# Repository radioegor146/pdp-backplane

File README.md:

# pdp-backplane

Custom PDP-11 Q22/Q22 backplane

All schematic is in KiCad

~~For now, not tested, so use on your own risk!~~

Tested, working!

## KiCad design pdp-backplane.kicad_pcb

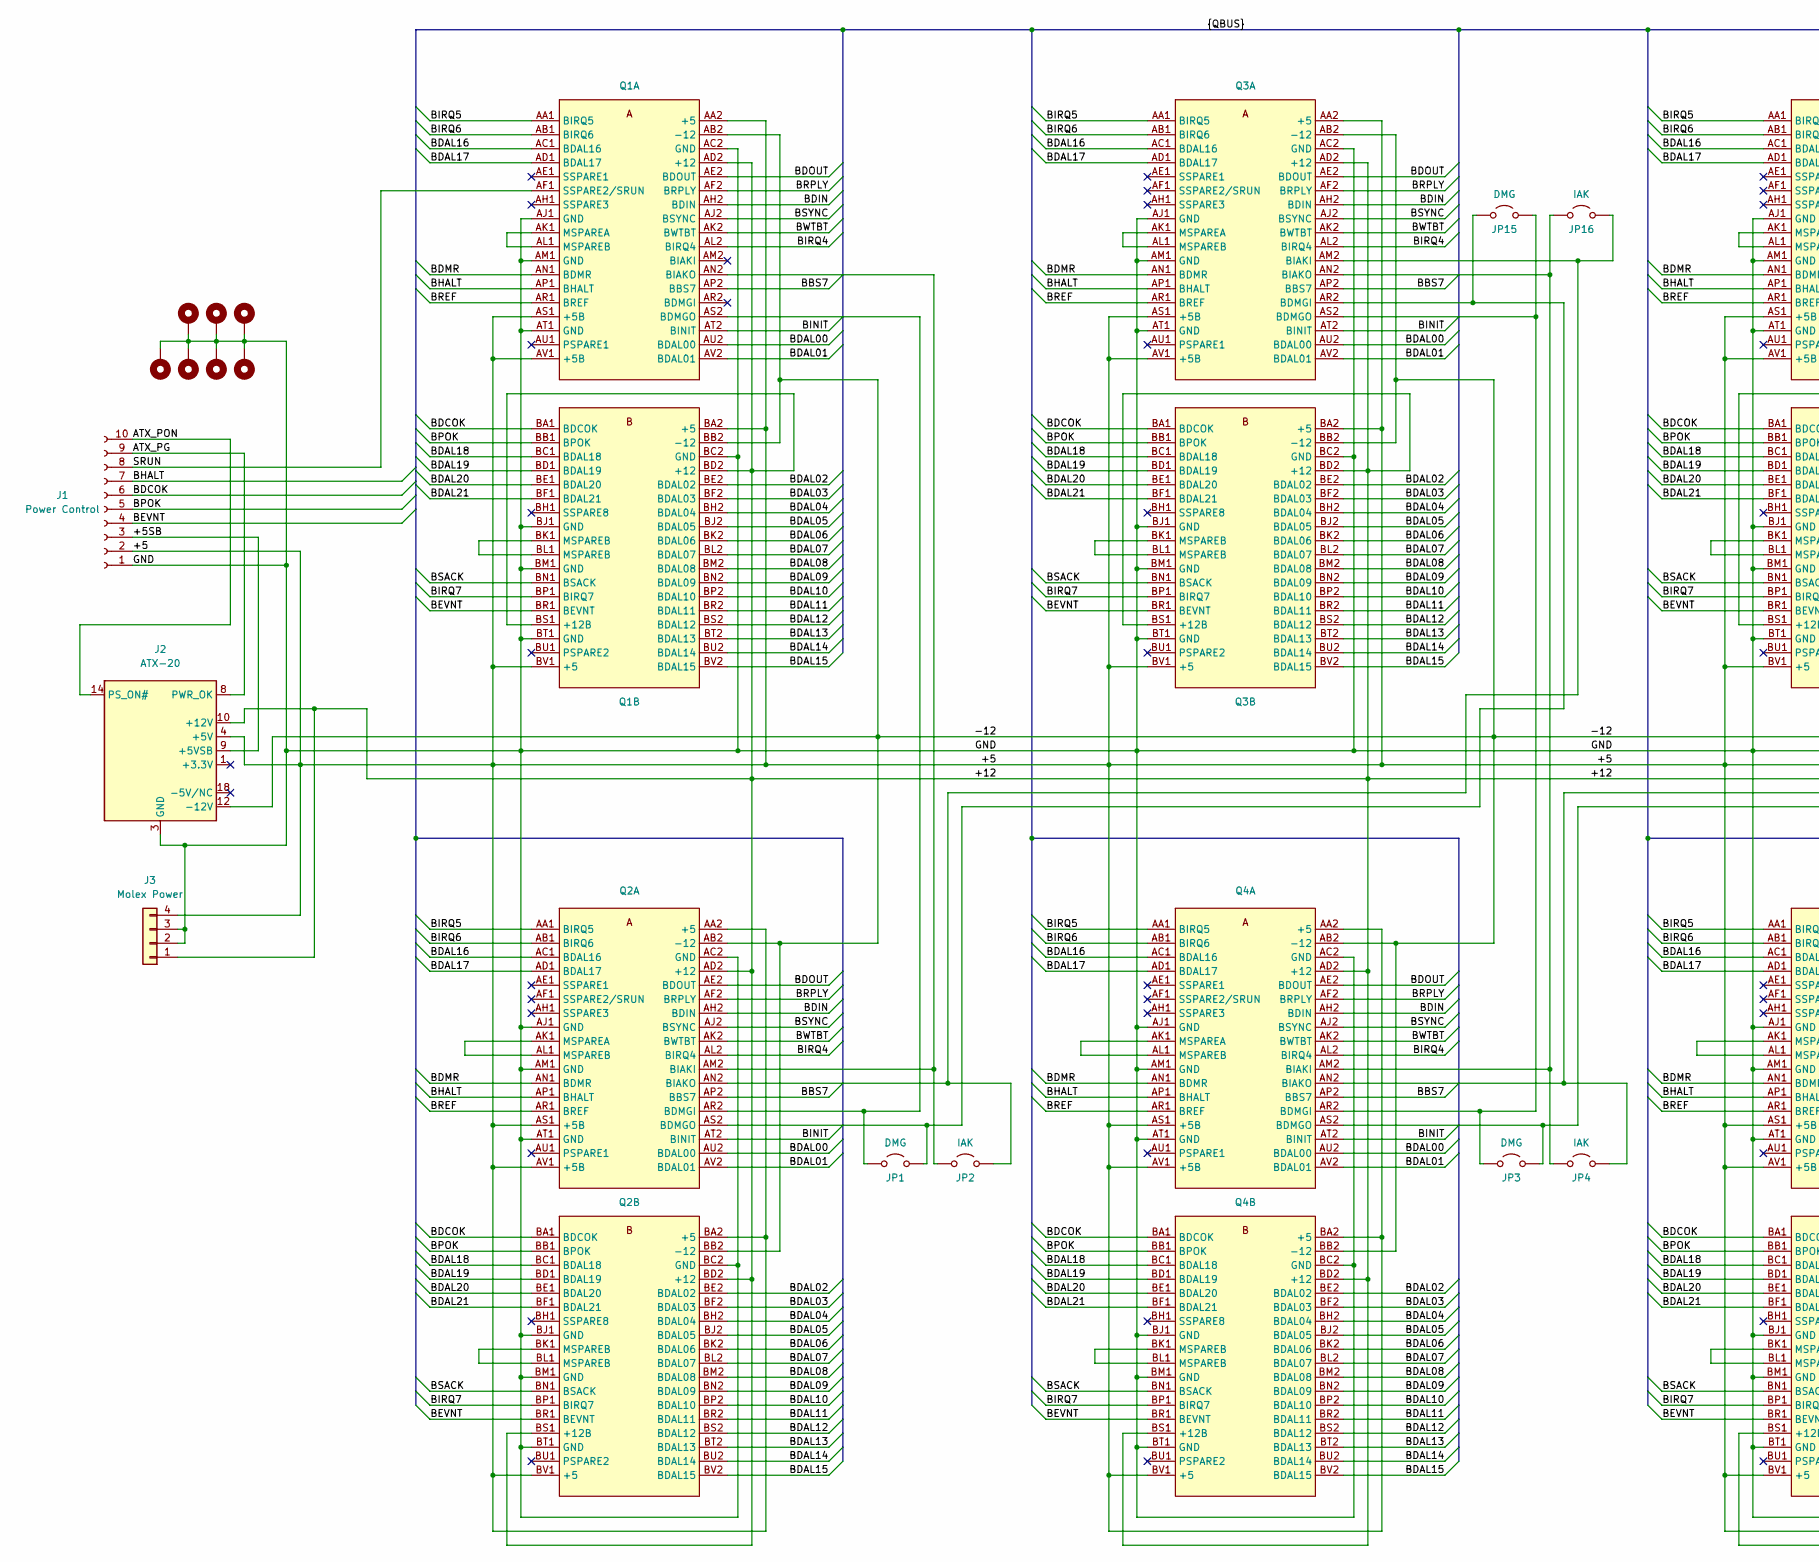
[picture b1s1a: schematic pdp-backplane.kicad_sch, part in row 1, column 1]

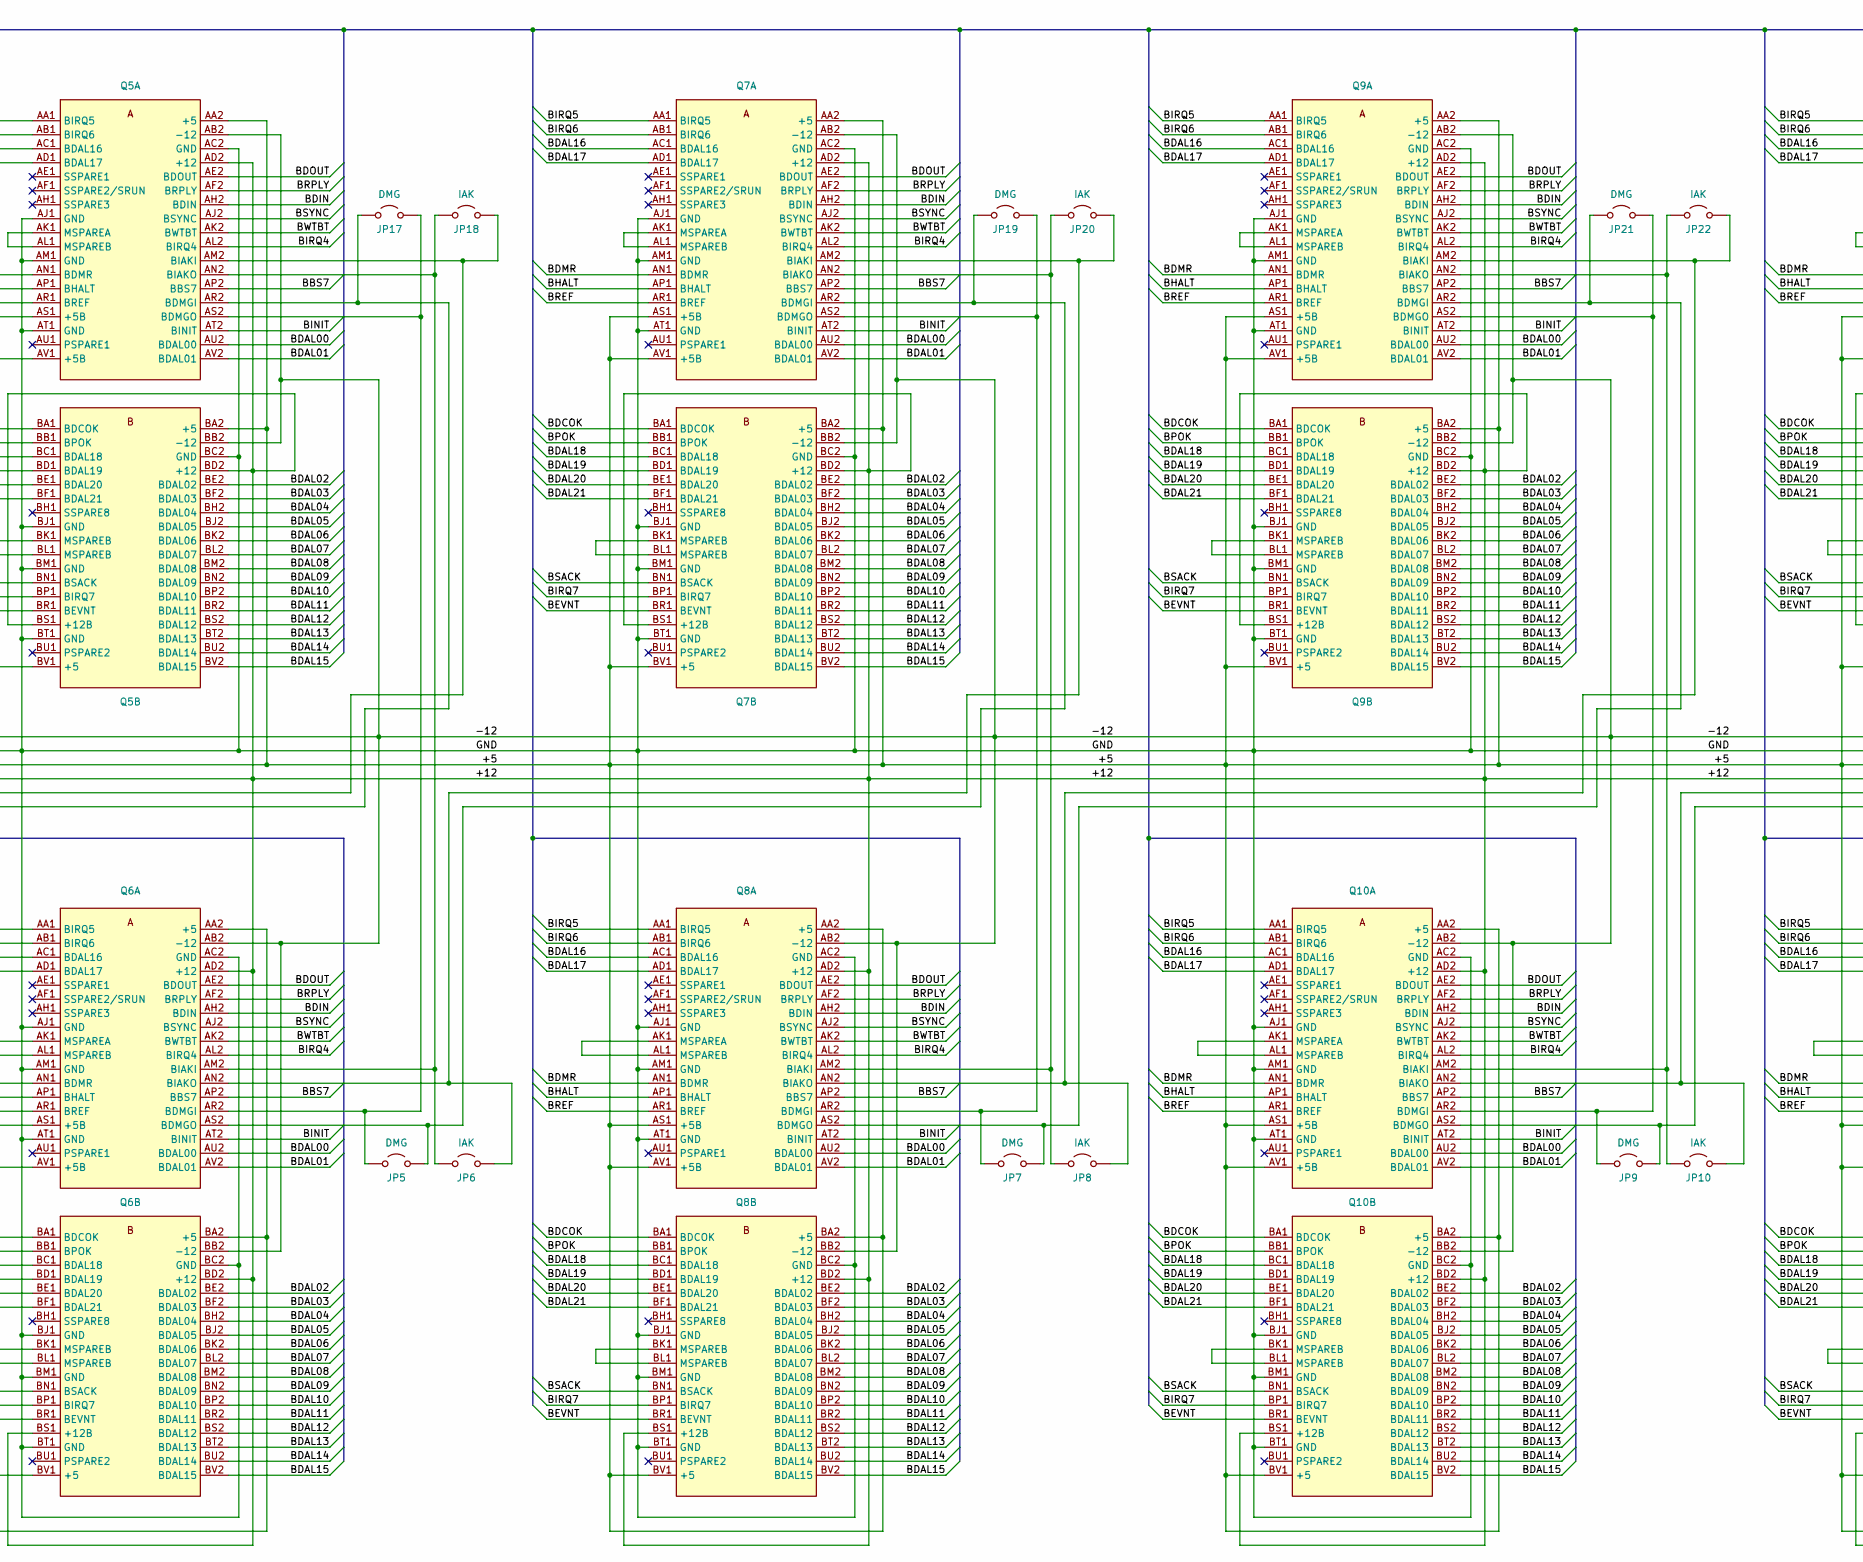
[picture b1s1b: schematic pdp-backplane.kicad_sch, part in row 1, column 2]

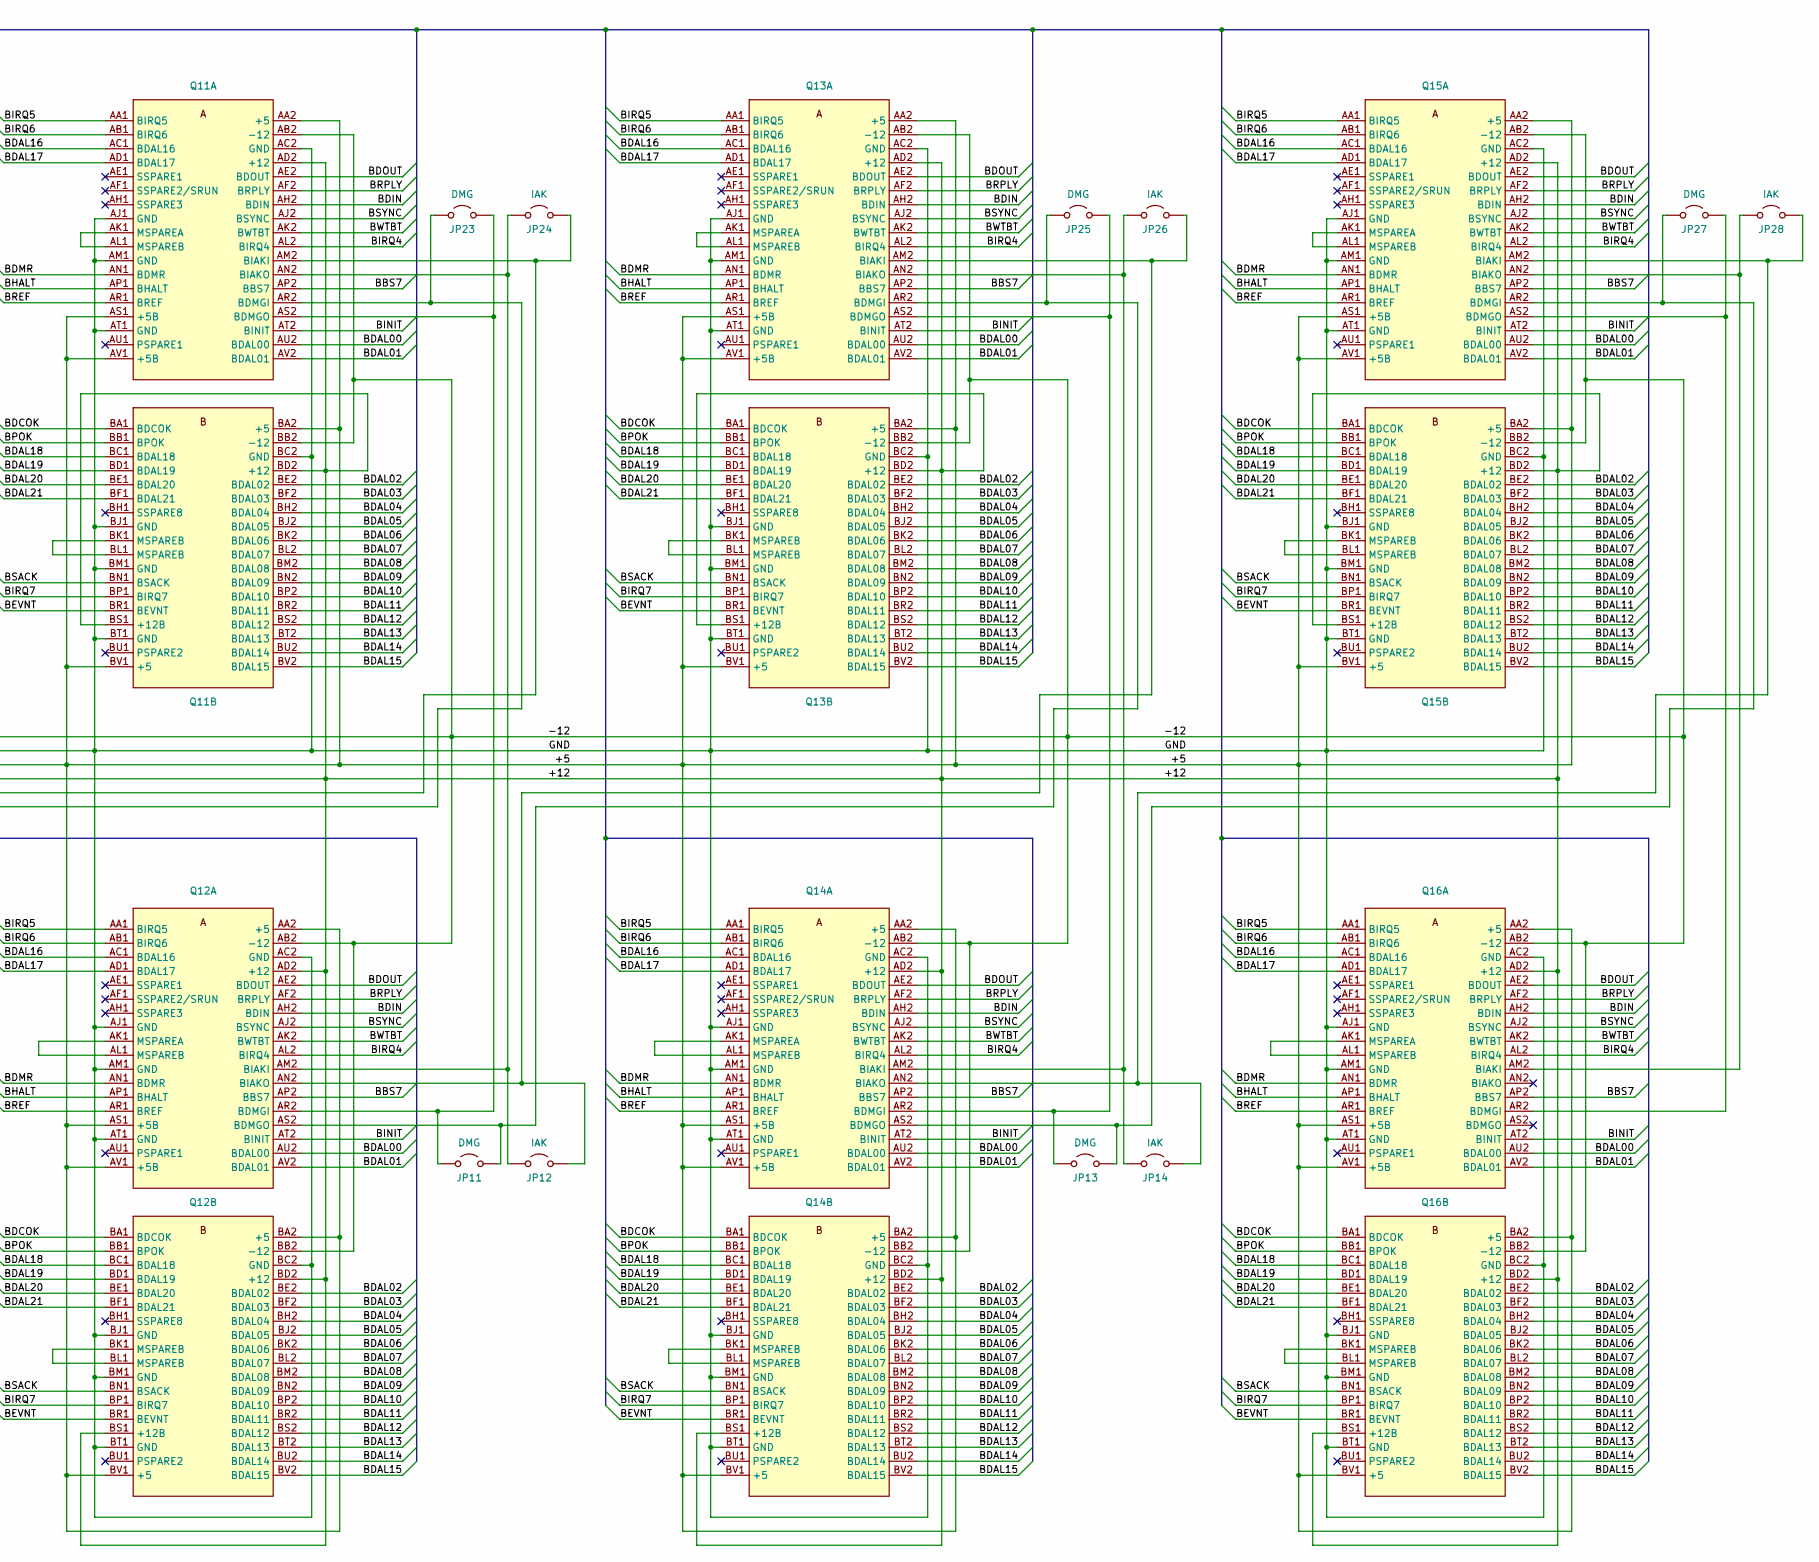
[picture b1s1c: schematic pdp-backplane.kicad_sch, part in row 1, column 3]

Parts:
H2, H3, H4, H5, H6, H7, H8: MountingHole_Pad; MountingHole_4.3mm_M4_Pad_TopBottom
J1: Power Control; JST_XH_B10B-XH-A_1x10_P2.50mm_Vertical
J2: ATX-20; Molex_Mini-Fit_Jr_5566-20A_2x10_P4.20mm_Vertical
J3: Molex Power; TE_MATE-N-LOK_350211-1_1x04_P5.08mm_Vertical
JP1, JP3, JP5, JP7, JP9, JP11, JP13, JP15, JP17, JP19, JP21, JP23, JP25, JP27: DMG; PinHeader_1x02_P2.54mm_Vertical
JP2, JP4, JP6, JP8, JP10, JP12, JP14, JP16, JP18, JP20, JP22, JP24, JP26, JP28: IAK; PinHeader_1x02_P2.54mm_Vertical
Q1, Q2, Q3, Q4, Q5, Q6, Q7, Q8, Q9, Q10, Q11, Q12, Q13, Q14, Q15, Q16: Bus_QBUS; QBus

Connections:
/+5: J1.2, J2.4 (+5V), J2.6 (+5V), J2.19 (+5V), J2.20 (+5V), J3.4, Q1.AA2 (+5), Q1.AS1 (+5B), Q1.AV1 (+5B), Q1.BA2 (+5), Q1.BV1 (+5), Q2.AA2 (+5), Q2.AS1 (+5B), Q2.AV1 (+5B), Q2.BA2 (+5), Q2.BV1 (+5), Q3.AA2 (+5), Q3.AS1 (+5B), Q3.AV1 (+5B), Q3.BA2 (+5), Q3.BV1 (+5), Q4.AA2 (+5), Q4.AS1 (+5B), Q4.AV1 (+5B), Q4.BA2 (+5), Q4.BV1 (+5), Q5.AA2 (+5), Q5.AS1 (+5B), Q5.AV1 (+5B), Q5.BA2 (+5), Q5.BV1 (+5), Q6.AA2 (+5), Q6.AS1 (+5B), Q6.AV1 (+5B), Q6.BA2 (+5), Q6.BV1 (+5), Q7.AA2 (+5), Q7.AS1 (+5B), Q7.AV1 (+5B), Q7.BA2 (+5), Q7.BV1 (+5), Q8.AA2 (+5), Q8.AS1 (+5B), Q8.AV1 (+5B), Q8.BA2 (+5), Q8.BV1 (+5), Q9.AA2 (+5), Q9.AS1 (+5B), Q9.AV1 (+5B), Q9.BA2 (+5), Q9.BV1 (+5), Q10.AA2 (+5), Q10.AS1 (+5B), Q10.AV1 (+5B), Q10.BA2 (+5), Q10.BV1 (+5), Q11.AA2 (+5), Q11.AS1 (+5B), Q11.AV1 (+5B), Q11.BA2 (+5), Q11.BV1 (+5), Q12.AA2 (+5), Q12.AS1 (+5B), Q12.AV1 (+5B), Q12.BA2 (+5), Q12.BV1 (+5), Q13.AA2 (+5), Q13.AS1 (+5B), Q13.AV1 (+5B), Q13.BA2 (+5), Q13.BV1 (+5), Q14.AA2 (+5), Q14.AS1 (+5B), Q14.AV1 (+5B), Q14.BA2 (+5), Q14.BV1 (+5), Q15.AA2 (+5), Q15.AS1 (+5B), Q15.AV1 (+5B), Q15.BA2 (+5), Q15.BV1 (+5), Q16.AA2 (+5), Q16.AS1 (+5B), Q16.AV1 (+5B), Q16.BA2 (+5), Q16.BV1 (+5)
/+5SB: J1.3, J2.9 (+5VSB)
/+12: J2.10 (+12V), J3.1, Q1.AD2 (+12), Q1.BD2 (+12), Q1.BS1 (+12B), Q2.AD2 (+12), Q2.BD2 (+12), Q2.BS1 (+12B), Q3.AD2 (+12), Q3.BD2 (+12), Q3.BS1 (+12B), Q4.AD2 (+12), Q4.BD2 (+12), Q4.BS1 (+12B), Q5.AD2 (+12), Q5.BD2 (+12), Q5.BS1 (+12B), Q6.AD2 (+12), Q6.BD2 (+12), Q6.BS1 (+12B), Q7.AD2 (+12), Q7.BD2 (+12), Q7.BS1 (+12B), Q8.AD2 (+12), Q8.BD2 (+12), Q8.BS1 (+12B), Q9.AD2 (+12), Q9.BD2 (+12), Q9.BS1 (+12B), Q10.AD2 (+12), Q10.BD2 (+12), Q10.BS1 (+12B), Q11.AD2 (+12), Q11.BD2 (+12), Q11.BS1 (+12B), Q12.AD2 (+12), Q12.BD2 (+12), Q12.BS1 (+12B), Q13.AD2 (+12), Q13.BD2 (+12), Q13.BS1 (+12B), Q14.AD2 (+12), Q14.BD2 (+12), Q14.BS1 (+12B), Q15.AD2 (+12), Q15.BD2 (+12), Q15.BS1 (+12B), Q16.AD2 (+12), Q16.BD2 (+12), Q16.BS1 (+12B)
/-12: J2.12 (-12V), Q1.AB2 (-12), Q1.BB2 (-12), Q2.AB2 (-12), Q2.BB2 (-12), Q3.AB2 (-12), Q3.BB2 (-12), Q4.AB2 (-12), Q4.BB2 (-12), Q5.AB2 (-12), Q5.BB2 (-12), Q6.AB2 (-12), Q6.BB2 (-12), Q7.AB2 (-12), Q7.BB2 (-12), Q8.AB2 (-12), Q8.BB2 (-12), Q9.AB2 (-12), Q9.BB2 (-12), Q10.AB2 (-12), Q10.BB2 (-12), Q11.AB2 (-12), Q11.BB2 (-12), Q12.AB2 (-12), Q12.BB2 (-12), Q13.AB2 (-12), Q13.BB2 (-12), Q14.AB2 (-12), Q14.BB2 (-12), Q15.AB2 (-12), Q15.BB2 (-12), Q16.AB2 (-12), Q16.BB2 (-12)
/ATX_PG: J1.9, J2.8 (PWR_OK)
/ATX_PON: J1.10, J2.14 (PS_ON#)
/BBS7: Q1.AP2 (BBS7), Q2.AP2 (BBS7), Q3.AP2 (BBS7), Q4.AP2 (BBS7), Q5.AP2 (BBS7), Q6.AP2 (BBS7), Q7.AP2 (BBS7), Q8.AP2 (BBS7), Q9.AP2 (BBS7), Q10.AP2 (BBS7), Q11.AP2 (BBS7), Q12.AP2 (BBS7), Q13.AP2 (BBS7), Q14.AP2 (BBS7), Q15.AP2 (BBS7), Q16.AP2 (BBS7)
/BDAL00: Q1.AU2 (BDAL00), Q2.AU2 (BDAL00), Q3.AU2 (BDAL00), Q4.AU2 (BDAL00), Q5.AU2 (BDAL00), Q6.AU2 (BDAL00), Q7.AU2 (BDAL00), Q8.AU2 (BDAL00), Q9.AU2 (BDAL00), Q10.AU2 (BDAL00), Q11.AU2 (BDAL00), Q12.AU2 (BDAL00), Q13.AU2 (BDAL00), Q14.AU2 (BDAL00), Q15.AU2 (BDAL00), Q16.AU2 (BDAL00)
/BDAL01: Q1.AV2 (BDAL01), Q2.AV2 (BDAL01), Q3.AV2 (BDAL01), Q4.AV2 (BDAL01), Q5.AV2 (BDAL01), Q6.AV2 (BDAL01), Q7.AV2 (BDAL01), Q8.AV2 (BDAL01), Q9.AV2 (BDAL01), Q10.AV2 (BDAL01), Q11.AV2 (BDAL01), Q12.AV2 (BDAL01), Q13.AV2 (BDAL01), Q14.AV2 (BDAL01), Q15.AV2 (BDAL01), Q16.AV2 (BDAL01)
/BDAL02: Q1.BE2 (BDAL02), Q2.BE2 (BDAL02), Q3.BE2 (BDAL02), Q4.BE2 (BDAL02), Q5.BE2 (BDAL02), Q6.BE2 (BDAL02), Q7.BE2 (BDAL02), Q8.BE2 (BDAL02), Q9.BE2 (BDAL02), Q10.BE2 (BDAL02), Q11.BE2 (BDAL02), Q12.BE2 (BDAL02), Q13.BE2 (BDAL02), Q14.BE2 (BDAL02), Q15.BE2 (BDAL02), Q16.BE2 (BDAL02)
/BDAL03: Q1.BF2 (BDAL03), Q2.BF2 (BDAL03), Q3.BF2 (BDAL03), Q4.BF2 (BDAL03), Q5.BF2 (BDAL03), Q6.BF2 (BDAL03), Q7.BF2 (BDAL03), Q8.BF2 (BDAL03), Q9.BF2 (BDAL03), Q10.BF2 (BDAL03), Q11.BF2 (BDAL03), Q12.BF2 (BDAL03), Q13.BF2 (BDAL03), Q14.BF2 (BDAL03), Q15.BF2 (BDAL03), Q16.BF2 (BDAL03)
/BDAL04: Q1.BH2 (BDAL04), Q2.BH2 (BDAL04), Q3.BH2 (BDAL04), Q4.BH2 (BDAL04), Q5.BH2 (BDAL04), Q6.BH2 (BDAL04), Q7.BH2 (BDAL04), Q8.BH2 (BDAL04), Q9.BH2 (BDAL04), Q10.BH2 (BDAL04), Q11.BH2 (BDAL04), Q12.BH2 (BDAL04), Q13.BH2 (BDAL04), Q14.BH2 (BDAL04), Q15.BH2 (BDAL04), Q16.BH2 (BDAL04)
/BDAL05: Q1.BJ2 (BDAL05), Q2.BJ2 (BDAL05), Q3.BJ2 (BDAL05), Q4.BJ2 (BDAL05), Q5.BJ2 (BDAL05), Q6.BJ2 (BDAL05), Q7.BJ2 (BDAL05), Q8.BJ2 (BDAL05), Q9.BJ2 (BDAL05), Q10.BJ2 (BDAL05), Q11.BJ2 (BDAL05), Q12.BJ2 (BDAL05), Q13.BJ2 (BDAL05), Q14.BJ2 (BDAL05), Q15.BJ2 (BDAL05), Q16.BJ2 (BDAL05)
/BDAL06: Q1.BK2 (BDAL06), Q2.BK2 (BDAL06), Q3.BK2 (BDAL06), Q4.BK2 (BDAL06), Q5.BK2 (BDAL06), Q6.BK2 (BDAL06), Q7.BK2 (BDAL06), Q8.BK2 (BDAL06), Q9.BK2 (BDAL06), Q10.BK2 (BDAL06), Q11.BK2 (BDAL06), Q12.BK2 (BDAL06), Q13.BK2 (BDAL06), Q14.BK2 (BDAL06), Q15.BK2 (BDAL06), Q16.BK2 (BDAL06)
/BDAL07: Q1.BL2 (BDAL07), Q2.BL2 (BDAL07), Q3.BL2 (BDAL07), Q4.BL2 (BDAL07), Q5.BL2 (BDAL07), Q6.BL2 (BDAL07), Q7.BL2 (BDAL07), Q8.BL2 (BDAL07), Q9.BL2 (BDAL07), Q10.BL2 (BDAL07), Q11.BL2 (BDAL07), Q12.BL2 (BDAL07), Q13.BL2 (BDAL07), Q14.BL2 (BDAL07), Q15.BL2 (BDAL07), Q16.BL2 (BDAL07)
/BDAL08: Q1.BM2 (BDAL08), Q2.BM2 (BDAL08), Q3.BM2 (BDAL08), Q4.BM2 (BDAL08), Q5.BM2 (BDAL08), Q6.BM2 (BDAL08), Q7.BM2 (BDAL08), Q8.BM2 (BDAL08), Q9.BM2 (BDAL08), Q10.BM2 (BDAL08), Q11.BM2 (BDAL08), Q12.BM2 (BDAL08), Q13.BM2 (BDAL08), Q14.BM2 (BDAL08), Q15.BM2 (BDAL08), Q16.BM2 (BDAL08)
/BDAL09: Q1.BN2 (BDAL09), Q2.BN2 (BDAL09), Q3.BN2 (BDAL09), Q4.BN2 (BDAL09), Q5.BN2 (BDAL09), Q6.BN2 (BDAL09), Q7.BN2 (BDAL09), Q8.BN2 (BDAL09), Q9.BN2 (BDAL09), Q10.BN2 (BDAL09), Q11.BN2 (BDAL09), Q12.BN2 (BDAL09), Q13.BN2 (BDAL09), Q14.BN2 (BDAL09), Q15.BN2 (BDAL09), Q16.BN2 (BDAL09)
/BDAL10: Q1.BP2 (BDAL10), Q2.BP2 (BDAL10), Q3.BP2 (BDAL10), Q4.BP2 (BDAL10), Q5.BP2 (BDAL10), Q6.BP2 (BDAL10), Q7.BP2 (BDAL10), Q8.BP2 (BDAL10), Q9.BP2 (BDAL10), Q10.BP2 (BDAL10), Q11.BP2 (BDAL10), Q12.BP2 (BDAL10), Q13.BP2 (BDAL10), Q14.BP2 (BDAL10), Q15.BP2 (BDAL10), Q16.BP2 (BDAL10)
/BDAL11: Q1.BR2 (BDAL11), Q2.BR2 (BDAL11), Q3.BR2 (BDAL11), Q4.BR2 (BDAL11), Q5.BR2 (BDAL11), Q6.BR2 (BDAL11), Q7.BR2 (BDAL11), Q8.BR2 (BDAL11), Q9.BR2 (BDAL11), Q10.BR2 (BDAL11), Q11.BR2 (BDAL11), Q12.BR2 (BDAL11), Q13.BR2 (BDAL11), Q14.BR2 (BDAL11), Q15.BR2 (BDAL11), Q16.BR2 (BDAL11)
/BDAL12: Q1.BS2 (BDAL12), Q2.BS2 (BDAL12), Q3.BS2 (BDAL12), Q4.BS2 (BDAL12), Q5.BS2 (BDAL12), Q6.BS2 (BDAL12), Q7.BS2 (BDAL12), Q8.BS2 (BDAL12), Q9.BS2 (BDAL12), Q10.BS2 (BDAL12), Q11.BS2 (BDAL12), Q12.BS2 (BDAL12), Q13.BS2 (BDAL12), Q14.BS2 (BDAL12), Q15.BS2 (BDAL12), Q16.BS2 (BDAL12)
/BDAL13: Q1.BT2 (BDAL13), Q2.BT2 (BDAL13), Q3.BT2 (BDAL13), Q4.BT2 (BDAL13), Q5.BT2 (BDAL13), Q6.BT2 (BDAL13), Q7.BT2 (BDAL13), Q8.BT2 (BDAL13), Q9.BT2 (BDAL13), Q10.BT2 (BDAL13), Q11.BT2 (BDAL13), Q12.BT2 (BDAL13), Q13.BT2 (BDAL13), Q14.BT2 (BDAL13), Q15.BT2 (BDAL13), Q16.BT2 (BDAL13)
/BDAL14: Q1.BU2 (BDAL14), Q2.BU2 (BDAL14), Q3.BU2 (BDAL14), Q4.BU2 (BDAL14), Q5.BU2 (BDAL14), Q6.BU2 (BDAL14), Q7.BU2 (BDAL14), Q8.BU2 (BDAL14), Q9.BU2 (BDAL14), Q10.BU2 (BDAL14), Q11.BU2 (BDAL14), Q12.BU2 (BDAL14), Q13.BU2 (BDAL14), Q14.BU2 (BDAL14), Q15.BU2 (BDAL14), Q16.BU2 (BDAL14)
/BDAL15: Q1.BV2 (BDAL15), Q2.BV2 (BDAL15), Q3.BV2 (BDAL15), Q4.BV2 (BDAL15), Q5.BV2 (BDAL15), Q6.BV2 (BDAL15), Q7.BV2 (BDAL15), Q8.BV2 (BDAL15), Q9.BV2 (BDAL15), Q10.BV2 (BDAL15), Q11.BV2 (BDAL15), Q12.BV2 (BDAL15), Q13.BV2 (BDAL15), Q14.BV2 (BDAL15), Q15.BV2 (BDAL15), Q16.BV2 (BDAL15)
/BDAL16: Q1.AC1 (BDAL16), Q2.AC1 (BDAL16), Q3.AC1 (BDAL16), Q4.AC1 (BDAL16), Q5.AC1 (BDAL16), Q6.AC1 (BDAL16), Q7.AC1 (BDAL16), Q8.AC1 (BDAL16), Q9.AC1 (BDAL16), Q10.AC1 (BDAL16), Q11.AC1 (BDAL16), Q12.AC1 (BDAL16), Q13.AC1 (BDAL16), Q14.AC1 (BDAL16), Q15.AC1 (BDAL16), Q16.AC1 (BDAL16)
/BDAL17: Q1.AD1 (BDAL17), Q2.AD1 (BDAL17), Q3.AD1 (BDAL17), Q4.AD1 (BDAL17), Q5.AD1 (BDAL17), Q6.AD1 (BDAL17), Q7.AD1 (BDAL17), Q8.AD1 (BDAL17), Q9.AD1 (BDAL17), Q10.AD1 (BDAL17), Q11.AD1 (BDAL17), Q12.AD1 (BDAL17), Q13.AD1 (BDAL17), Q14.AD1 (BDAL17), Q15.AD1 (BDAL17), Q16.AD1 (BDAL17)
/BDAL18: Q1.BC1 (BDAL18), Q2.BC1 (BDAL18), Q3.BC1 (BDAL18), Q4.BC1 (BDAL18), Q5.BC1 (BDAL18), Q6.BC1 (BDAL18), Q7.BC1 (BDAL18), Q8.BC1 (BDAL18), Q9.BC1 (BDAL18), Q10.BC1 (BDAL18), Q11.BC1 (BDAL18), Q12.BC1 (BDAL18), Q13.BC1 (BDAL18), Q14.BC1 (BDAL18), Q15.BC1 (BDAL18), Q16.BC1 (BDAL18)
/BDAL19: Q1.BD1 (BDAL19), Q2.BD1 (BDAL19), Q3.BD1 (BDAL19), Q4.BD1 (BDAL19), Q5.BD1 (BDAL19), Q6.BD1 (BDAL19), Q7.BD1 (BDAL19), Q8.BD1 (BDAL19), Q9.BD1 (BDAL19), Q10.BD1 (BDAL19), Q11.BD1 (BDAL19), Q12.BD1 (BDAL19), Q13.BD1 (BDAL19), Q14.BD1 (BDAL19), Q15.BD1 (BDAL19), Q16.BD1 (BDAL19)
/BDAL20: Q1.BE1 (BDAL20), Q2.BE1 (BDAL20), Q3.BE1 (BDAL20), Q4.BE1 (BDAL20), Q5.BE1 (BDAL20), Q6.BE1 (BDAL20), Q7.BE1 (BDAL20), Q8.BE1 (BDAL20), Q9.BE1 (BDAL20), Q10.BE1 (BDAL20), Q11.BE1 (BDAL20), Q12.BE1 (BDAL20), Q13.BE1 (BDAL20), Q14.BE1 (BDAL20), Q15.BE1 (BDAL20), Q16.BE1 (BDAL20)
/BDAL21: Q1.BF1 (BDAL21), Q2.BF1 (BDAL21), Q3.BF1 (BDAL21), Q4.BF1 (BDAL21), Q5.BF1 (BDAL21), Q6.BF1 (BDAL21), Q7.BF1 (BDAL21), Q8.BF1 (BDAL21), Q9.BF1 (BDAL21), Q10.BF1 (BDAL21), Q11.BF1 (BDAL21), Q12.BF1 (BDAL21), Q13.BF1 (BDAL21), Q14.BF1 (BDAL21), Q15.BF1 (BDAL21), Q16.BF1 (BDAL21)
/BDCOK: J1.6, Q1.BA1 (BDCOK), Q2.BA1 (BDCOK), Q3.BA1 (BDCOK), Q4.BA1 (BDCOK), Q5.BA1 (BDCOK), Q6.BA1 (BDCOK), Q7.BA1 (BDCOK), Q8.BA1 (BDCOK), Q9.BA1 (BDCOK), Q10.BA1 (BDCOK), Q11.BA1 (BDCOK), Q12.BA1 (BDCOK), Q13.BA1 (BDCOK), Q14.BA1 (BDCOK), Q15.BA1 (BDCOK), Q16.BA1 (BDCOK)
/BDIN: Q1.AH2 (BDIN), Q2.AH2 (BDIN), Q3.AH2 (BDIN), Q4.AH2 (BDIN), Q5.AH2 (BDIN), Q6.AH2 (BDIN), Q7.AH2 (BDIN), Q8.AH2 (BDIN), Q9.AH2 (BDIN), Q10.AH2 (BDIN), Q11.AH2 (BDIN), Q12.AH2 (BDIN), Q13.AH2 (BDIN), Q14.AH2 (BDIN), Q15.AH2 (BDIN), Q16.AH2 (BDIN)
/BDMR: Q1.AN1 (BDMR), Q2.AN1 (BDMR), Q3.AN1 (BDMR), Q4.AN1 (BDMR), Q5.AN1 (BDMR), Q6.AN1 (BDMR), Q7.AN1 (BDMR), Q8.AN1 (BDMR), Q9.AN1 (BDMR), Q10.AN1 (BDMR), Q11.AN1 (BDMR), Q12.AN1 (BDMR), Q13.AN1 (BDMR), Q14.AN1 (BDMR), Q15.AN1 (BDMR), Q16.AN1 (BDMR)
/BDOUT: Q1.AE2 (BDOUT), Q2.AE2 (BDOUT), Q3.AE2 (BDOUT), Q4.AE2 (BDOUT), Q5.AE2 (BDOUT), Q6.AE2 (BDOUT), Q7.AE2 (BDOUT), Q8.AE2 (BDOUT), Q9.AE2 (BDOUT), Q10.AE2 (BDOUT), Q11.AE2 (BDOUT), Q12.AE2 (BDOUT), Q13.AE2 (BDOUT), Q14.AE2 (BDOUT), Q15.AE2 (BDOUT), Q16.AE2 (BDOUT)
/BEVNT: J1.4, Q1.BR1 (BEVNT), Q2.BR1 (BEVNT), Q3.BR1 (BEVNT), Q4.BR1 (BEVNT), Q5.BR1 (BEVNT), Q6.BR1 (BEVNT), Q7.BR1 (BEVNT), Q8.BR1 (BEVNT), Q9.BR1 (BEVNT), Q10.BR1 (BEVNT), Q11.BR1 (BEVNT), Q12.BR1 (BEVNT), Q13.BR1 (BEVNT), Q14.BR1 (BEVNT), Q15.BR1 (BEVNT), Q16.BR1 (BEVNT)
/BHALT: J1.7, Q1.AP1 (BHALT), Q2.AP1 (BHALT), Q3.AP1 (BHALT), Q4.AP1 (BHALT), Q5.AP1 (BHALT), Q6.AP1 (BHALT), Q7.AP1 (BHALT), Q8.AP1 (BHALT), Q9.AP1 (BHALT), Q10.AP1 (BHALT), Q11.AP1 (BHALT), Q12.AP1 (BHALT), Q13.AP1 (BHALT), Q14.AP1 (BHALT), Q15.AP1 (BHALT), Q16.AP1 (BHALT)
/BINIT: Q1.AT2 (BINIT), Q2.AT2 (BINIT), Q3.AT2 (BINIT), Q4.AT2 (BINIT), Q5.AT2 (BINIT), Q6.AT2 (BINIT), Q7.AT2 (BINIT), Q8.AT2 (BINIT), Q9.AT2 (BINIT), Q10.AT2 (BINIT), Q11.AT2 (BINIT), Q12.AT2 (BINIT), Q13.AT2 (BINIT), Q14.AT2 (BINIT), Q15.AT2 (BINIT), Q16.AT2 (BINIT)
/BIRQ4: Q1.AL2 (BIRQ4), Q2.AL2 (BIRQ4), Q3.AL2 (BIRQ4), Q4.AL2 (BIRQ4), Q5.AL2 (BIRQ4), Q6.AL2 (BIRQ4), Q7.AL2 (BIRQ4), Q8.AL2 (BIRQ4), Q9.AL2 (BIRQ4), Q10.AL2 (BIRQ4), Q11.AL2 (BIRQ4), Q12.AL2 (BIRQ4), Q13.AL2 (BIRQ4), Q14.AL2 (BIRQ4), Q15.AL2 (BIRQ4), Q16.AL2 (BIRQ4)
/BIRQ5: Q1.AA1 (BIRQ5), Q2.AA1 (BIRQ5), Q3.AA1 (BIRQ5), Q4.AA1 (BIRQ5), Q5.AA1 (BIRQ5), Q6.AA1 (BIRQ5), Q7.AA1 (BIRQ5), Q8.AA1 (BIRQ5), Q9.AA1 (BIRQ5), Q10.AA1 (BIRQ5), Q11.AA1 (BIRQ5), Q12.AA1 (BIRQ5), Q13.AA1 (BIRQ5), Q14.AA1 (BIRQ5), Q15.AA1 (BIRQ5), Q16.AA1 (BIRQ5)
/BIRQ6: Q1.AB1 (BIRQ6), Q2.AB1 (BIRQ6), Q3.AB1 (BIRQ6), Q4.AB1 (BIRQ6), Q5.AB1 (BIRQ6), Q6.AB1 (BIRQ6), Q7.AB1 (BIRQ6), Q8.AB1 (BIRQ6), Q9.AB1 (BIRQ6), Q10.AB1 (BIRQ6), Q11.AB1 (BIRQ6), Q12.AB1 (BIRQ6), Q13.AB1 (BIRQ6), Q14.AB1 (BIRQ6), Q15.AB1 (BIRQ6), Q16.AB1 (BIRQ6)
/BIRQ7: Q1.BP1 (BIRQ7), Q2.BP1 (BIRQ7), Q3.BP1 (BIRQ7), Q4.BP1 (BIRQ7), Q5.BP1 (BIRQ7), Q6.BP1 (BIRQ7), Q7.BP1 (BIRQ7), Q8.BP1 (BIRQ7), Q9.BP1 (BIRQ7), Q10.BP1 (BIRQ7), Q11.BP1 (BIRQ7), Q12.BP1 (BIRQ7), Q13.BP1 (BIRQ7), Q14.BP1 (BIRQ7), Q15.BP1 (BIRQ7), Q16.BP1 (BIRQ7)
/BPOK: J1.5, Q1.BB1 (BPOK), Q2.BB1 (BPOK), Q3.BB1 (BPOK), Q4.BB1 (BPOK), Q5.BB1 (BPOK), Q6.BB1 (BPOK), Q7.BB1 (BPOK), Q8.BB1 (BPOK), Q9.BB1 (BPOK), Q10.BB1 (BPOK), Q11.BB1 (BPOK), Q12.BB1 (BPOK), Q13.BB1 (BPOK), Q14.BB1 (BPOK), Q15.BB1 (BPOK), Q16.BB1 (BPOK)
/BREF: Q1.AR1 (BREF), Q2.AR1 (BREF), Q3.AR1 (BREF), Q4.AR1 (BREF), Q5.AR1 (BREF), Q6.AR1 (BREF), Q7.AR1 (BREF), Q8.AR1 (BREF), Q9.AR1 (BREF), Q10.AR1 (BREF), Q11.AR1 (BREF), Q12.AR1 (BREF), Q13.AR1 (BREF), Q14.AR1 (BREF), Q15.AR1 (BREF), Q16.AR1 (BREF)
/BRPLY: Q1.AF2 (BRPLY), Q2.AF2 (BRPLY), Q3.AF2 (BRPLY), Q4.AF2 (BRPLY), Q5.AF2 (BRPLY), Q6.AF2 (BRPLY), Q7.AF2 (BRPLY), Q8.AF2 (BRPLY), Q9.AF2 (BRPLY), Q10.AF2 (BRPLY), Q11.AF2 (BRPLY), Q12.AF2 (BRPLY), Q13.AF2 (BRPLY), Q14.AF2 (BRPLY), Q15.AF2 (BRPLY), Q16.AF2 (BRPLY)
/BSACK: Q1.BN1 (BSACK), Q2.BN1 (BSACK), Q3.BN1 (BSACK), Q4.BN1 (BSACK), Q5.BN1 (BSACK), Q6.BN1 (BSACK), Q7.BN1 (BSACK), Q8.BN1 (BSACK), Q9.BN1 (BSACK), Q10.BN1 (BSACK), Q11.BN1 (BSACK), Q12.BN1 (BSACK), Q13.BN1 (BSACK), Q14.BN1 (BSACK), Q15.BN1 (BSACK), Q16.BN1 (BSACK)
/BSYNC: Q1.AJ2 (BSYNC), Q2.AJ2 (BSYNC), Q3.AJ2 (BSYNC), Q4.AJ2 (BSYNC), Q5.AJ2 (BSYNC), Q6.AJ2 (BSYNC), Q7.AJ2 (BSYNC), Q8.AJ2 (BSYNC), Q9.AJ2 (BSYNC), Q10.AJ2 (BSYNC), Q11.AJ2 (BSYNC), Q12.AJ2 (BSYNC), Q13.AJ2 (BSYNC), Q14.AJ2 (BSYNC), Q15.AJ2 (BSYNC), Q16.AJ2 (BSYNC)
/BWTBT: Q1.AK2 (BWTBT), Q2.AK2 (BWTBT), Q3.AK2 (BWTBT), Q4.AK2 (BWTBT), Q5.AK2 (BWTBT), Q6.AK2 (BWTBT), Q7.AK2 (BWTBT), Q8.AK2 (BWTBT), Q9.AK2 (BWTBT), Q10.AK2 (BWTBT), Q11.AK2 (BWTBT), Q12.AK2 (BWTBT), Q13.AK2 (BWTBT), Q14.AK2 (BWTBT), Q15.AK2 (BWTBT), Q16.AK2 (BWTBT)
/GND: H2.1, H3.1, H4.1, H5.1, H6.1, H7.1, H8.1, J1.1, J2.3 (GND), J2.5 (GND), J2.7 (GND), J2.13 (GND), J2.15 (GND), J2.16 (GND), J2.17 (GND), J3.2, J3.3, Q1.AC2 (GND), Q1.AJ1 (GND), Q1.AM1 (GND), Q1.AT1 (GND), Q1.BC2 (GND), Q1.BJ1 (GND), Q1.BM1 (GND), Q1.BT1 (GND), Q2.AC2 (GND), Q2.AJ1 (GND), Q2.AM1 (GND), Q2.AT1 (GND), Q2.BC2 (GND), Q2.BJ1 (GND), Q2.BM1 (GND), Q2.BT1 (GND), Q3.AC2 (GND), Q3.AJ1 (GND), Q3.AM1 (GND), Q3.AT1 (GND), Q3.BC2 (GND), Q3.BJ1 (GND), Q3.BM1 (GND), Q3.BT1 (GND), Q4.AC2 (GND), Q4.AJ1 (GND), Q4.AM1 (GND), Q4.AT1 (GND), Q4.BC2 (GND), Q4.BJ1 (GND), Q4.BM1 (GND), Q4.BT1 (GND), Q5.AC2 (GND), Q5.AJ1 (GND), Q5.AM1 (GND), Q5.AT1 (GND), Q5.BC2 (GND), Q5.BJ1 (GND), Q5.BM1 (GND), Q5.BT1 (GND), Q6.AC2 (GND), Q6.AJ1 (GND), Q6.AM1 (GND), Q6.AT1 (GND), Q6.BC2 (GND), Q6.BJ1 (GND), Q6.BM1 (GND), Q6.BT1 (GND), Q7.AC2 (GND), Q7.AJ1 (GND), Q7.AM1 (GND), Q7.AT1 (GND), Q7.BC2 (GND), Q7.BJ1 (GND), Q7.BM1 (GND), Q7.BT1 (GND), Q8.AC2 (GND), Q8.AJ1 (GND), Q8.AM1 (GND), Q8.AT1 (GND), Q8.BC2 (GND), Q8.BJ1 (GND), Q8.BM1 (GND), Q8.BT1 (GND), Q9.AC2 (GND), Q9.AJ1 (GND), Q9.AM1 (GND), Q9.AT1 (GND), Q9.BC2 (GND), Q9.BJ1 (GND), Q9.BM1 (GND), Q9.BT1 (GND), Q10.AC2 (GND), Q10.AJ1 (GND), Q10.AM1 (GND), Q10.AT1 (GND), Q10.BC2 (GND), Q10.BJ1 (GND), Q10.BM1 (GND), Q10.BT1 (GND), Q11.AC2 (GND), Q11.AJ1 (GND), Q11.AM1 (GND), Q11.AT1 (GND), Q11.BC2 (GND), Q11.BJ1 (GND), Q11.BM1 (GND), Q11.BT1 (GND), Q12.AC2 (GND), Q12.AJ1 (GND), Q12.AM1 (GND), Q12.AT1 (GND), Q12.BC2 (GND), Q12.BJ1 (GND), Q12.BM1 (GND), Q12.BT1 (GND), Q13.AC2 (GND), Q13.AJ1 (GND), Q13.AM1 (GND), Q13.AT1 (GND), Q13.BC2 (GND), Q13.BJ1 (GND), Q13.BM1 (GND), Q13.BT1 (GND), Q14.AC2 (GND), Q14.AJ1 (GND), Q14.AM1 (GND), Q14.AT1 (GND), Q14.BC2 (GND), Q14.BJ1 (GND), Q14.BM1 (GND), Q14.BT1 (GND), Q15.AC2 (GND), Q15.AJ1 (GND), Q15.AM1 (GND), Q15.AT1 (GND), Q15.BC2 (GND), Q15.BJ1 (GND), Q15.BM1 (GND), Q15.BT1 (GND), Q16.AC2 (GND), Q16.AJ1 (GND), Q16.AM1 (GND), Q16.AT1 (GND), Q16.BC2 (GND), Q16.BJ1 (GND), Q16.BM1 (GND), Q16.BT1 (GND)
/SRUN: J1.8, Q1.AF1 (SSPARE2/SRUN)
unnamed: JP1.1 (A), Q1.AS2 (BDMGO), Q2.AR2 (BDMGI)
unnamed: JP1.2 (B), JP15.1 (A), Q2.AS2 (BDMGO), Q3.AR2 (BDMGI)
unnamed: JP2.1 (A), Q1.AN2 (BIAKO), Q2.AM2 (BIAKI)
unnamed: JP10.1 (A), JP22.2 (B), Q9.AN2 (BIAKO), Q10.AM2 (BIAKI)
unnamed: JP10.2 (B), JP24.1 (A), Q10.AN2 (BIAKO), Q11.AM2 (BIAKI)
unnamed: JP11.1 (A), JP23.2 (B), Q11.AS2 (BDMGO), Q12.AR2 (BDMGI)
unnamed: JP11.2 (B), JP25.1 (A), Q12.AS2 (BDMGO), Q13.AR2 (BDMGI)
unnamed: JP12.1 (A), JP24.2 (B), Q11.AN2 (BIAKO), Q12.AM2 (BIAKI)
unnamed: JP12.2 (B), JP26.1 (A), Q12.AN2 (BIAKO), Q13.AM2 (BIAKI)
unnamed: JP13.1 (A), JP25.2 (B), Q13.AS2 (BDMGO), Q14.AR2 (BDMGI)
unnamed: JP13.2 (B), JP27.1 (A), Q14.AS2 (BDMGO), Q15.AR2 (BDMGI)
unnamed: JP14.1 (A), JP26.2 (B), Q13.AN2 (BIAKO), Q14.AM2 (BIAKI)
unnamed: JP14.2 (B), JP28.1 (A), Q14.AN2 (BIAKO), Q15.AM2 (BIAKI)
unnamed: JP3.1 (A), JP15.2 (B), Q3.AS2 (BDMGO), Q4.AR2 (BDMGI)
unnamed: JP2.2 (B), JP16.1 (A), Q2.AN2 (BIAKO), Q3.AM2 (BIAKI)
unnamed: JP4.1 (A), JP16.2 (B), Q3.AN2 (BIAKO), Q4.AM2 (BIAKI)
unnamed: JP3.2 (B), JP17.1 (A), Q4.AS2 (BDMGO), Q5.AR2 (BDMGI)
unnamed: JP5.1 (A), JP17.2 (B), Q5.AS2 (BDMGO), Q6.AR2 (BDMGI)
unnamed: JP4.2 (B), JP18.1 (A), Q4.AN2 (BIAKO), Q5.AM2 (BIAKI)
unnamed: JP6.1 (A), JP18.2 (B), Q5.AN2 (BIAKO), Q6.AM2 (BIAKI)
unnamed: JP5.2 (B), JP19.1 (A), Q6.AS2 (BDMGO), Q7.AR2 (BDMGI)
unnamed: JP7.1 (A), JP19.2 (B), Q7.AS2 (BDMGO), Q8.AR2 (BDMGI)
unnamed: JP6.2 (B), JP20.1 (A), Q6.AN2 (BIAKO), Q7.AM2 (BIAKI)
unnamed: JP8.1 (A), JP20.2 (B), Q7.AN2 (BIAKO), Q8.AM2 (BIAKI)
unnamed: JP7.2 (B), JP21.1 (A), Q8.AS2 (BDMGO), Q9.AR2 (BDMGI)
unnamed: JP9.1 (A), JP21.2 (B), Q9.AS2 (BDMGO), Q10.AR2 (BDMGI)
unnamed: JP8.2 (B), JP22.1 (A), Q8.AN2 (BIAKO), Q9.AM2 (BIAKI)
unnamed: JP9.2 (B), JP23.1 (A), Q10.AS2 (BDMGO), Q11.AR2 (BDMGI)
unnamed: JP27.2 (B), Q15.AS2 (BDMGO), Q16.AR2 (BDMGI)
unnamed: JP28.2 (B), Q15.AN2 (BIAKO), Q16.AM2 (BIAKI)
unnamed: Q1.AK1 (MSPAREA), Q1.AL1 (MSPAREB)
unnamed: Q1.BK1 (MSPAREB), Q1.BL1 (MSPAREB)
unnamed: Q2.AK1 (MSPAREA), Q2.AL1 (MSPAREB)
unnamed: Q2.BK1 (MSPAREB), Q2.BL1 (MSPAREB)
unnamed: Q3.AK1 (MSPAREA), Q3.AL1 (MSPAREB)
unnamed: Q3.BK1 (MSPAREB), Q3.BL1 (MSPAREB)
unnamed: Q4.AK1 (MSPAREA), Q4.AL1 (MSPAREB)
unnamed: Q4.BK1 (MSPAREB), Q4.BL1 (MSPAREB)
unnamed: Q5.AK1 (MSPAREA), Q5.AL1 (MSPAREB)
unnamed: Q5.BK1 (MSPAREB), Q5.BL1 (MSPAREB)
unnamed: Q6.AK1 (MSPAREA), Q6.AL1 (MSPAREB)
unnamed: Q6.BK1 (MSPAREB), Q6.BL1 (MSPAREB)
unnamed: Q7.AK1 (MSPAREA), Q7.AL1 (MSPAREB)
unnamed: Q7.BK1 (MSPAREB), Q7.BL1 (MSPAREB)
unnamed: Q8.AK1 (MSPAREA), Q8.AL1 (MSPAREB)
unnamed: Q8.BK1 (MSPAREB), Q8.BL1 (MSPAREB)
unnamed: Q9.AK1 (MSPAREA), Q9.AL1 (MSPAREB)
unnamed: Q9.BK1 (MSPAREB), Q9.BL1 (MSPAREB)
unnamed: Q10.AK1 (MSPAREA), Q10.AL1 (MSPAREB)
unnamed: Q10.BK1 (MSPAREB), Q10.BL1 (MSPAREB)
unnamed: Q11.AK1 (MSPAREA), Q11.AL1 (MSPAREB)
unnamed: Q11.BK1 (MSPAREB), Q11.BL1 (MSPAREB)
unnamed: Q12.AK1 (MSPAREA), Q12.AL1 (MSPAREB)
unnamed: Q12.BK1 (MSPAREB), Q12.BL1 (MSPAREB)
unnamed: Q13.AK1 (MSPAREA), Q13.AL1 (MSPAREB)
unnamed: Q13.BK1 (MSPAREB), Q13.BL1 (MSPAREB)
unnamed: Q14.AK1 (MSPAREA), Q14.AL1 (MSPAREB)
unnamed: Q14.BK1 (MSPAREB), Q14.BL1 (MSPAREB)
unnamed: Q15.AK1 (MSPAREA), Q15.AL1 (MSPAREB)
unnamed: Q15.BK1 (MSPAREB), Q15.BL1 (MSPAREB)
unnamed: Q16.AK1 (MSPAREA), Q16.AL1 (MSPAREB)
unnamed: Q16.BK1 (MSPAREB), Q16.BL1 (MSPAREB)

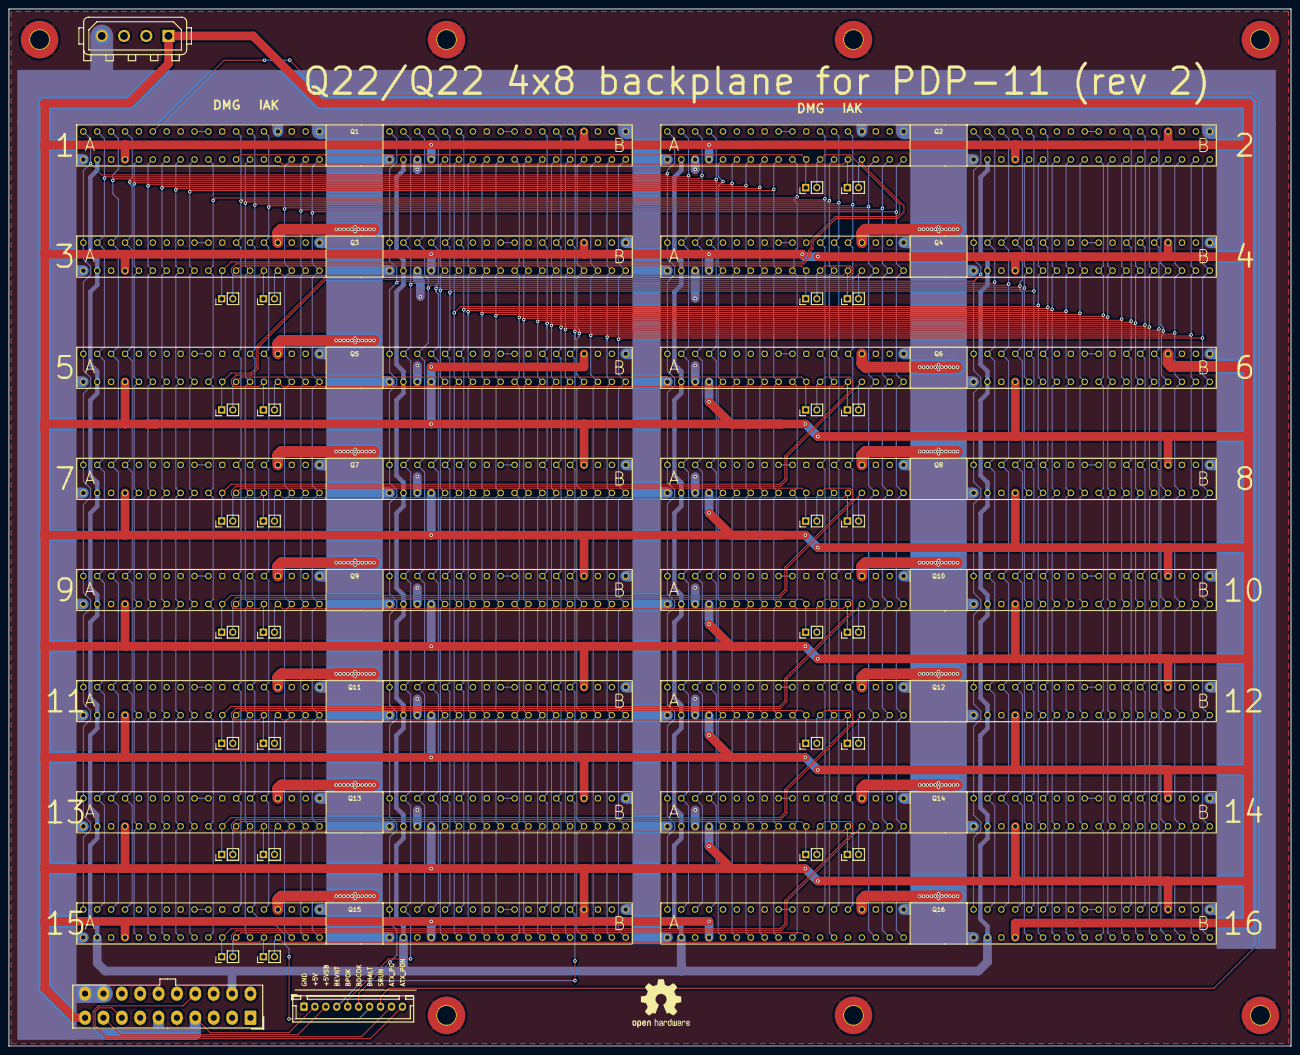
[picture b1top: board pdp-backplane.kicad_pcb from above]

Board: 2 copper layers, 293.0 x 237.0 mm, 54 parts (0 on the bottom side), 110 nets.

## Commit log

2024-06-27 main commit
2024-06-27 add readme
2025-06-13 add: new version
